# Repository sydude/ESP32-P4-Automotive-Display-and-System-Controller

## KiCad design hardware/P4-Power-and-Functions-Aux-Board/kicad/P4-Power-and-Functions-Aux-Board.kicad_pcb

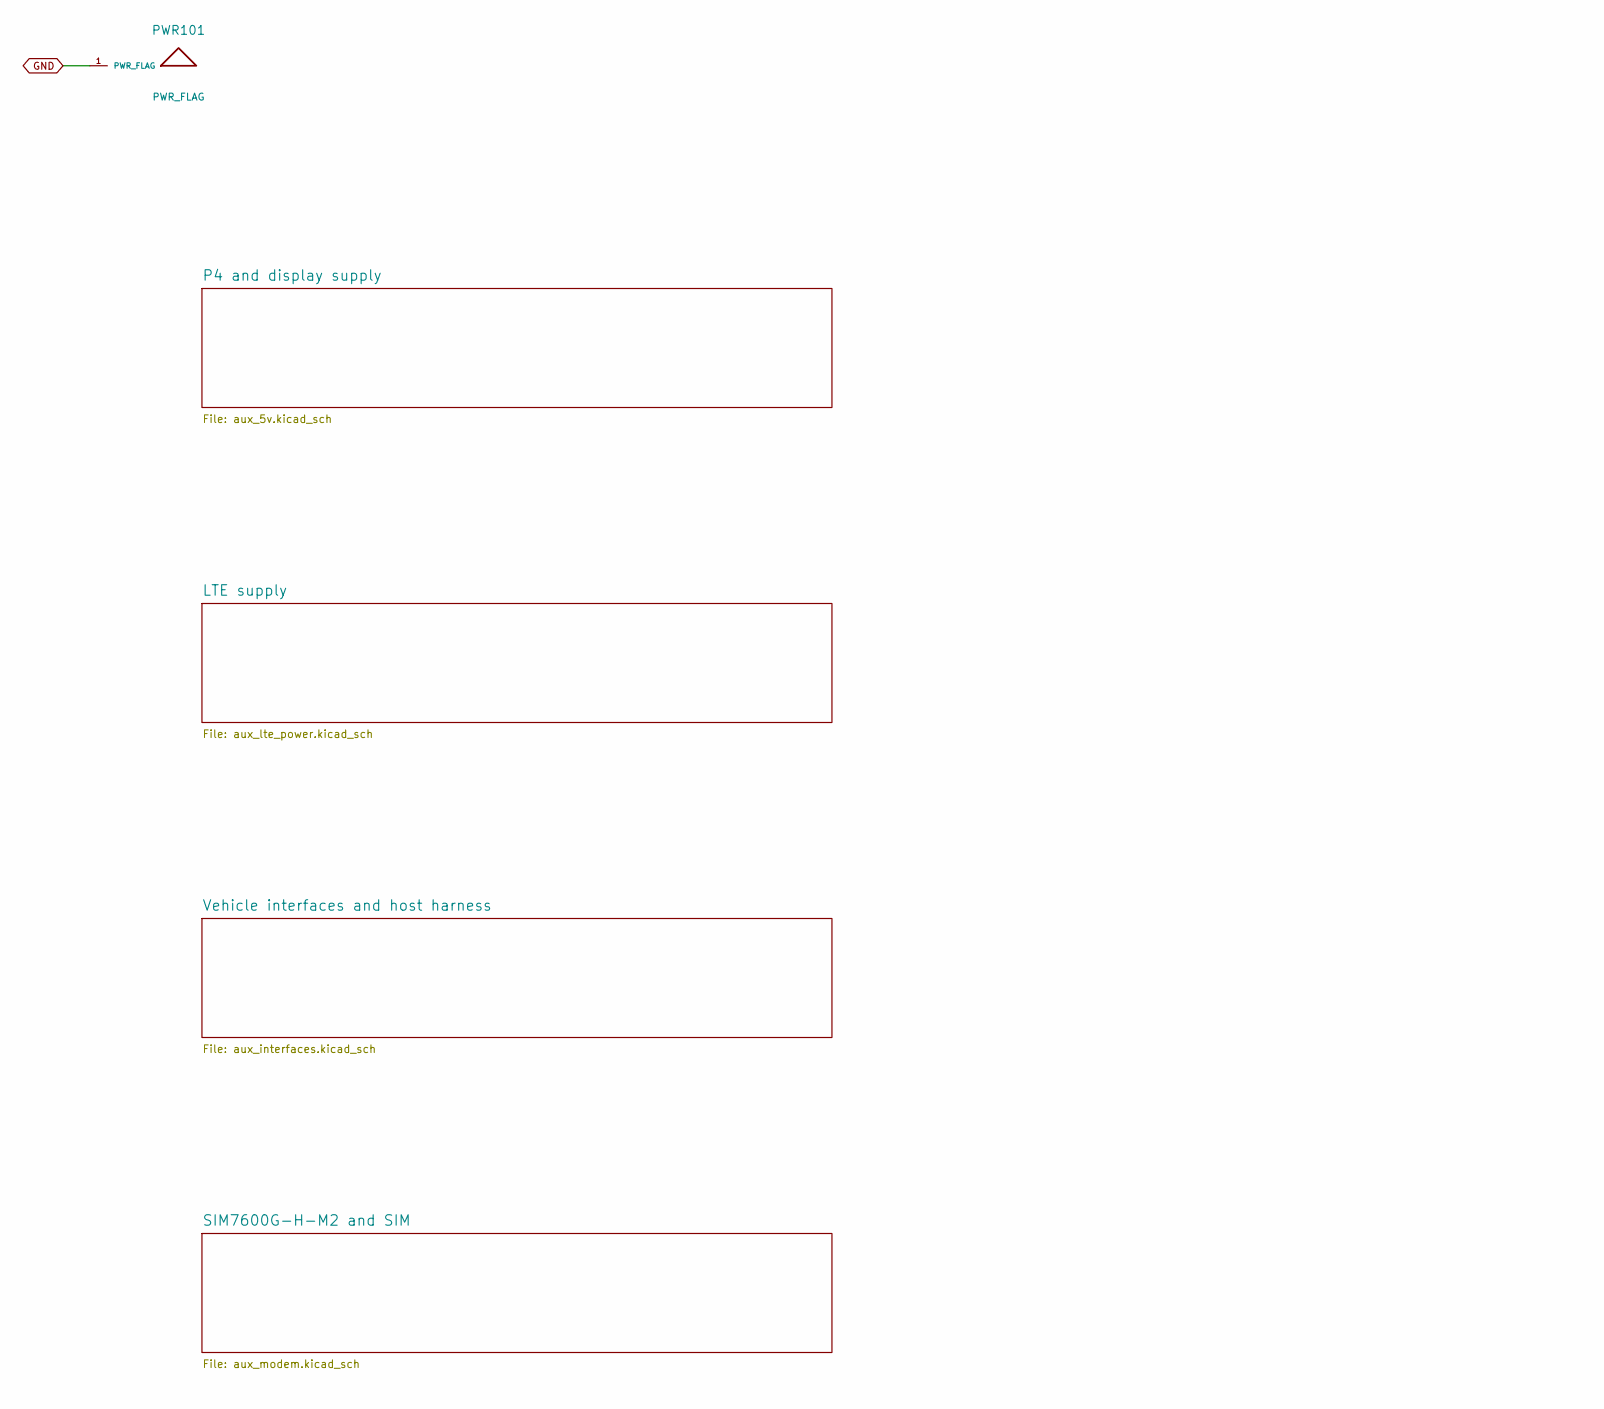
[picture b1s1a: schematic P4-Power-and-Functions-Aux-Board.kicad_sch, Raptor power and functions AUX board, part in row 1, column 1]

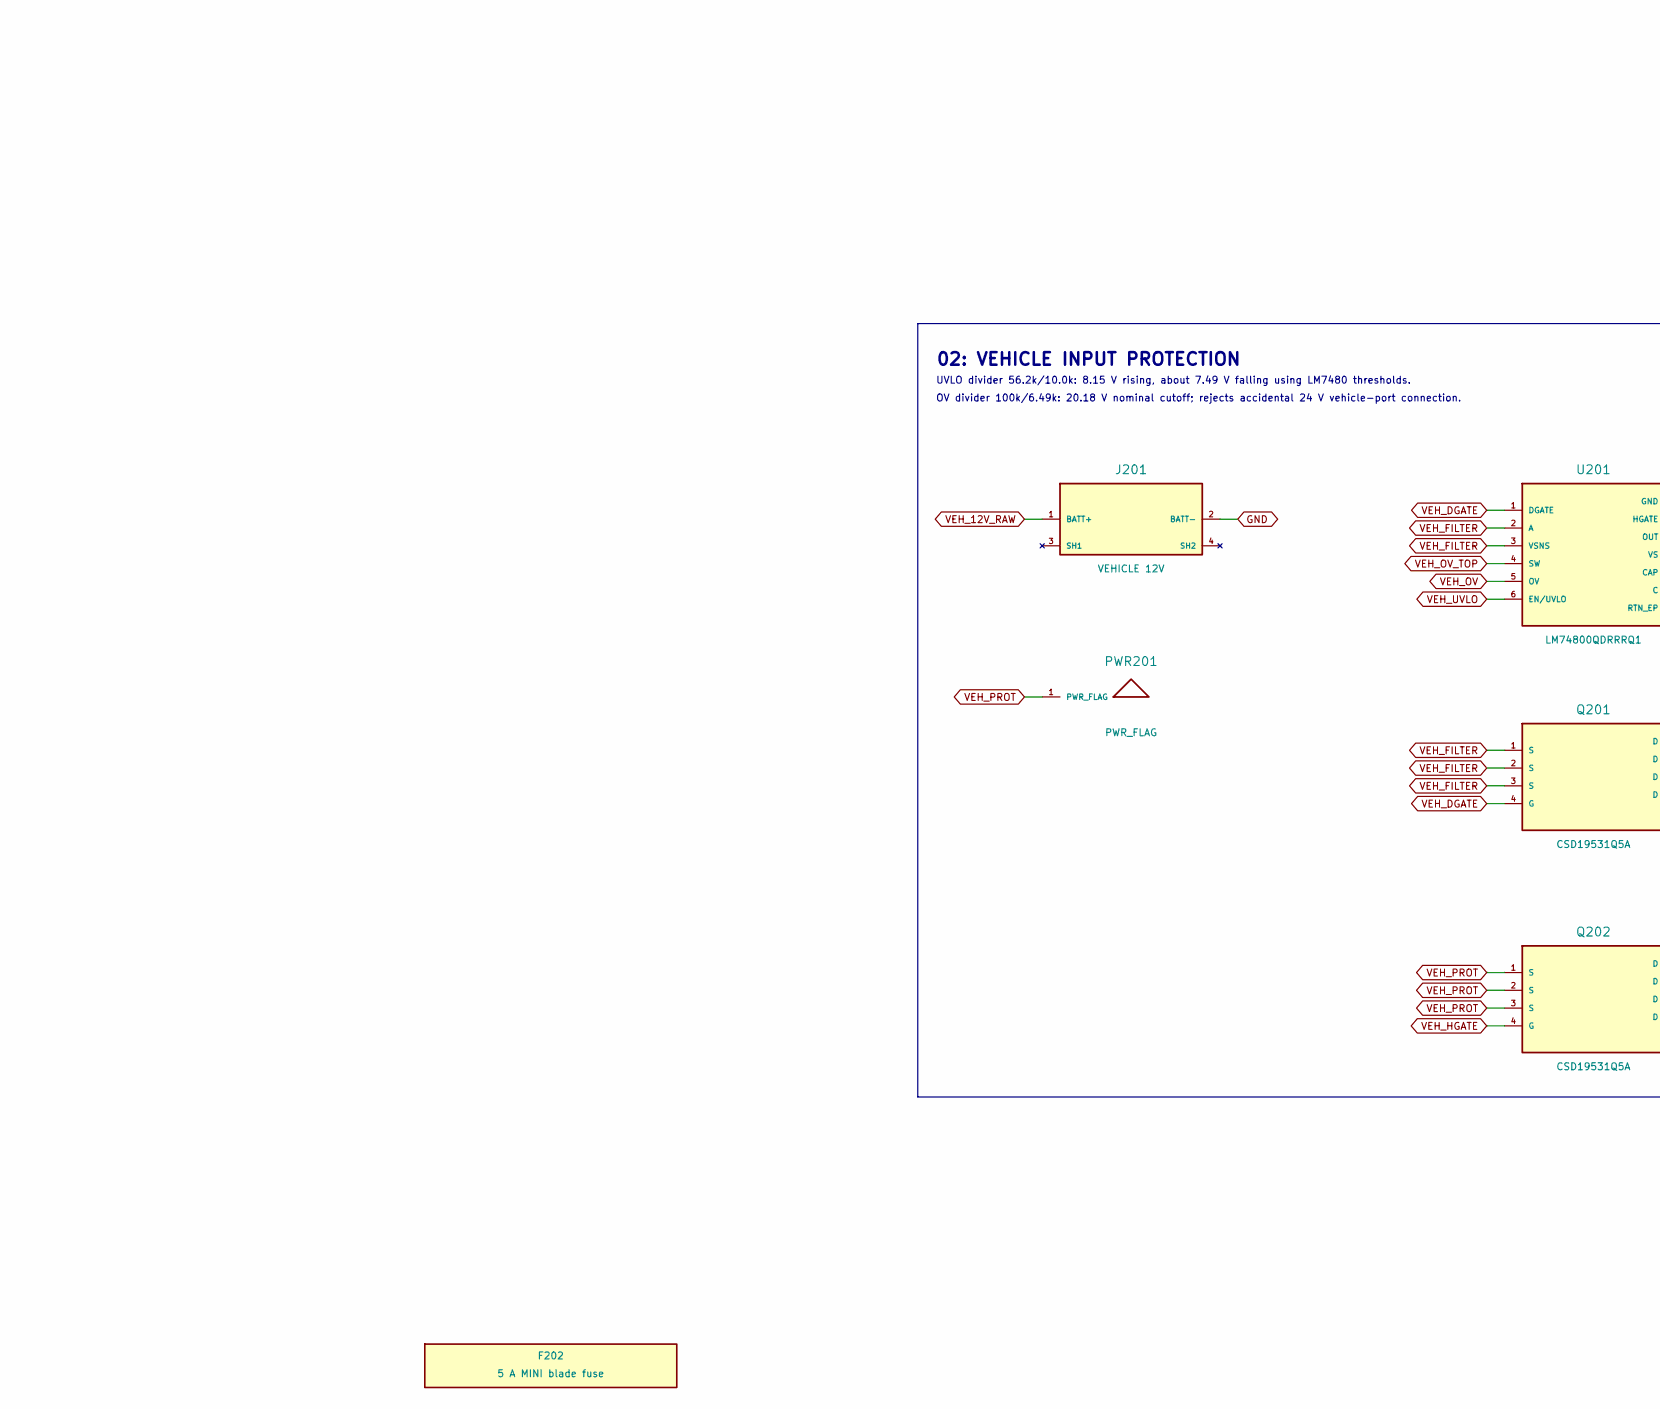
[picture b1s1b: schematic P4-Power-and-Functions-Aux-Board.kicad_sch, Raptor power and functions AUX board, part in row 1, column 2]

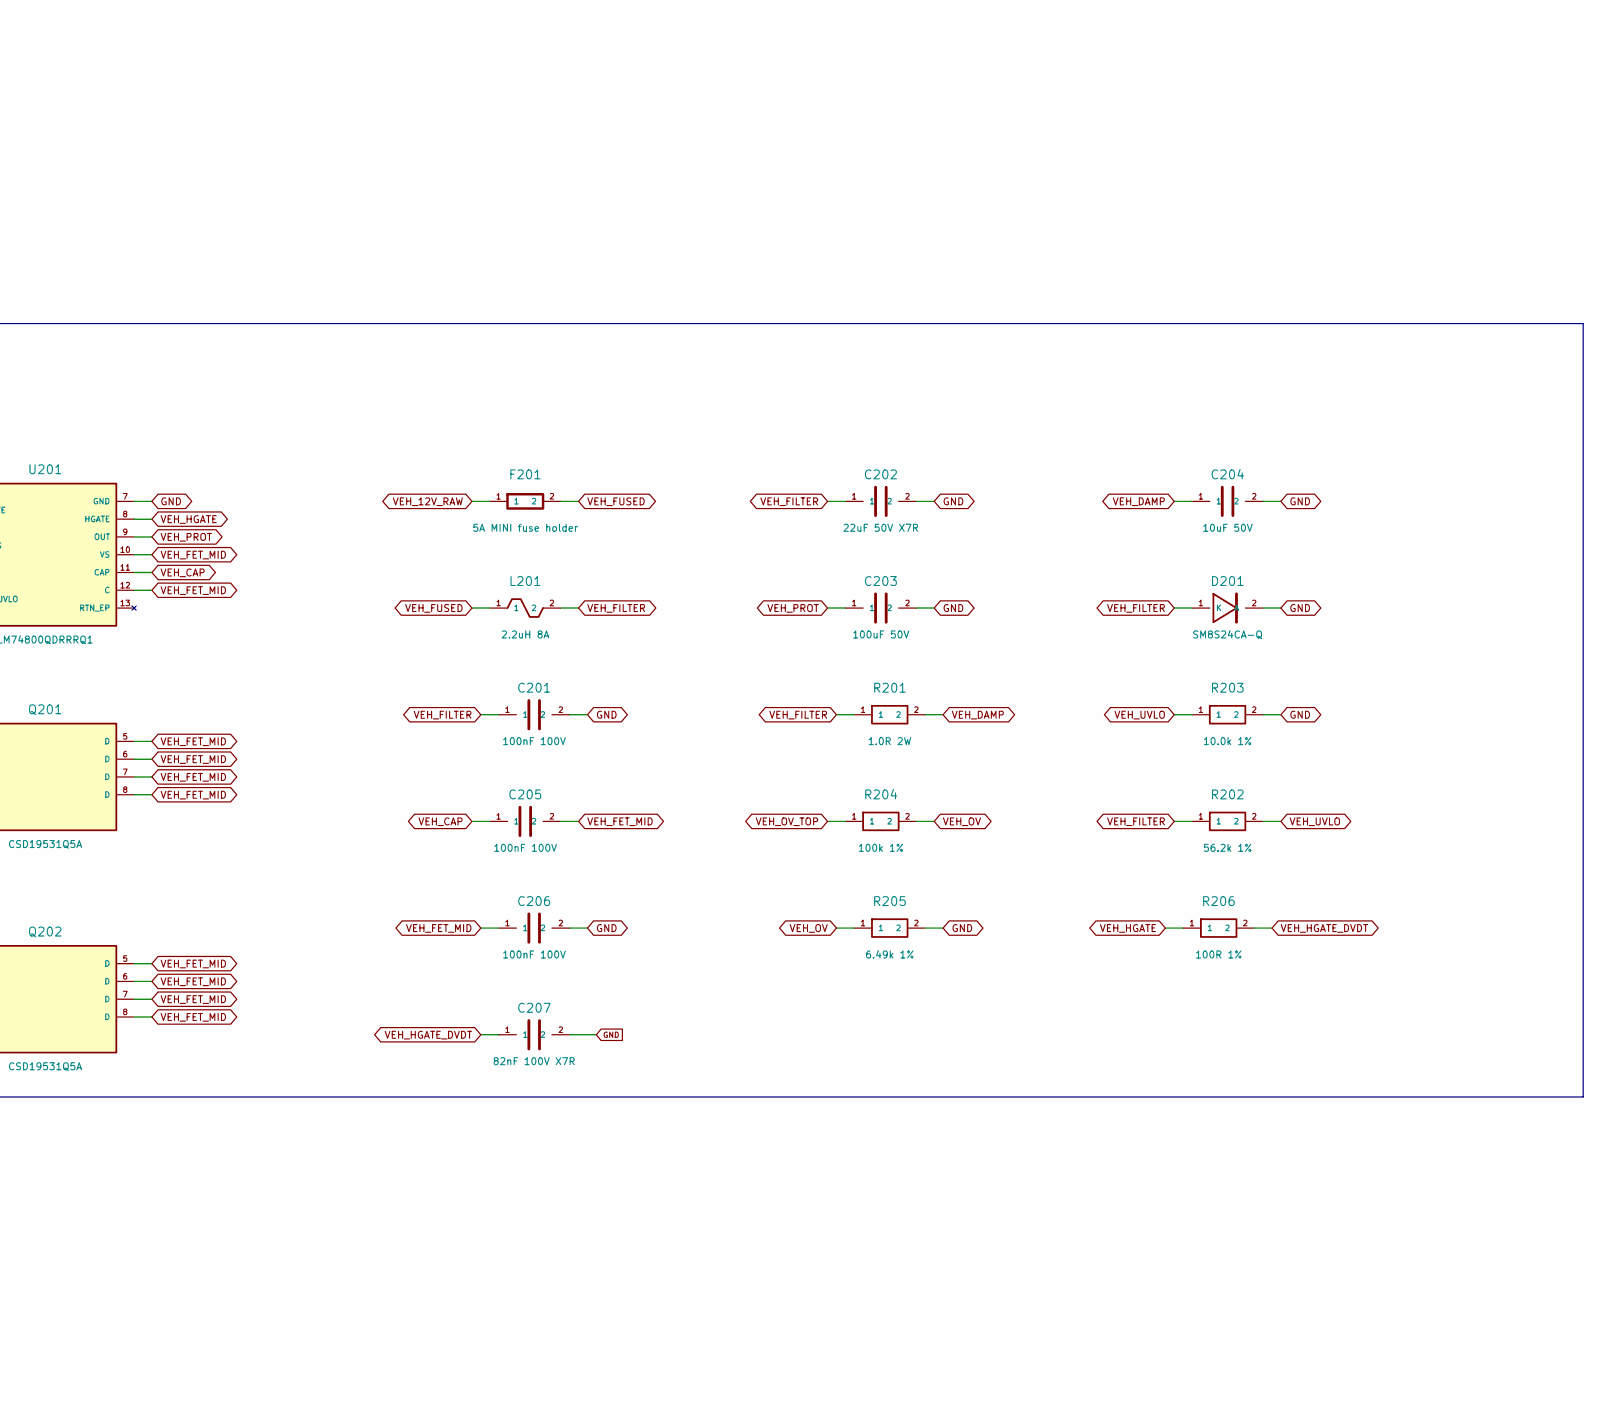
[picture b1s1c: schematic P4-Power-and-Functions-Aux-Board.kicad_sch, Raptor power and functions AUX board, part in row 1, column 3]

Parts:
C201, C205, C206: 100nF 100V; C_0603_1608Metric; MPN GCM188R72A104KA64D; LCSC C415406
C202: 22uF 50V X7R; C_1812_4532Metric; MPN FS43X226K500ERG; LCSC C22388553
C203: 100uF 50V; CP_Elec_10x10; MPN MAL215097101E3; LCSC C2163037
C204: 10uF 50V; C_1210_3225Metric; MPN GRM32ER71H106KA12L; LCSC C77102
C207: 82nF 100V X7R; C_0603_1608Metric; MPN C0603C823K1RACAUTO; LCSC C19862796
D201: SM8S24CA-Q; Bourns_DO-218AB; MPN SM8S24CA-Q; LCSC C1976790
F201: 5A MINI fuse holder; Fuseholder_Blade_Mini_Keystone_3568; MPN 3568; LCSC C5249699
F202: 5 A MINI blade fuse; MPN 0297005.WXNV; LCSC C151093
J201: VEHICLE 12V; CONN_SD-43045-007_02_MOL; MPN 43045-0218; LCSC C476811
L201: 2.2uH 8A; L_Bourns_SRP1038A_10.0x10.0mm; MPN SRP1038A-2R2M; LCSC C2042353
PWR101, PWR201: PWR_FLAG
Q201, Q202: CSD19531Q5A; Texas_DQJ0008A_VSONP-8; MPN CSD19531Q5A; LCSC C2760462
R201: 1.0R 2W; R_2512_6332Metric; MPN CRH2512F1R00E04S; LCSC C2832126
R202: 56.2k 1%; R_0603_1608Metric; MPN AF0603FR-0756K2L; LCSC C1882617
R203: 10.0k 1%; R_0603_1608Metric; MPN AC0603FR-0710KL; LCSC C116677
R204: 100k 1%; R_0603_1608Metric; MPN AC0603FR-07100KL; LCSC C116674
R205: 6.49k 1%; R_0603_1608Metric; MPN RC0603FR-076K49L; LCSC C163421
R206: 100R 1%; R_0603_1608Metric; MPN ERJ-3EKF1000V; LCSC C193336
U201: LM74800QDRRRQ1; Texas_DRR0012E_WSON-12_3x3mm_P0.5mm_EP1.3x2.5mm; MPN LM74800QDRRRQ1; LCSC C3215600

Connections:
GND: C201.2, C202.2, C203.2, C204.2, C206.2, C207.2, D201.2 (A), J201.2 (BATT-), PWR101.1, R203.2, R205.2, U201.7 (GND); also elsewhere on the board
VEH_12V_RAW: F201.1, J201.1 (BATT+)
VEH_CAP: C205.1, U201.11 (CAP)
VEH_DAMP: C204.1, R201.2
VEH_DGATE: Q201.4 (G), U201.1 (DGATE)
VEH_FET_MID: C205.2, C206.1, Q201.5 (D), Q201.6 (D), Q201.7 (D), Q201.8 (D), Q202.5 (D), Q202.6 (D), Q202.7 (D), Q202.8 (D), U201.10 (VS), U201.12 (C)
VEH_FILTER: C201.1, C202.1, D201.1 (K), L201.2, Q201.1 (S), Q201.2 (S), Q201.3 (S), R201.1, R202.1, U201.2 (A), U201.3 (VSNS)
VEH_FUSED: F201.2, L201.1
VEH_HGATE: Q202.4 (G), R206.1, U201.8 (HGATE)
VEH_HGATE_DVDT: C207.1, R206.2
VEH_OV: R204.2, R205.1, U201.5 (OV)
VEH_OV_TOP: R204.1, U201.4 (SW)
VEH_PROT: C203.1, PWR201.1, Q202.1 (S), Q202.2 (S), Q202.3 (S), U201.9 (OUT); also elsewhere on the board
VEH_UVLO: R202.2, R203.1, U201.6 (EN/UVLO)

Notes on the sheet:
02: VEHICLE INPUT PROTECTION
OV divider 100k/6.49k: 20.18 V nominal cutoff; rejects accidental 24 V vehicle-port connection.
UVLO divider 56.2k/10.0k: 8.15 V rising, about 7.49 V falling using LM7480 thresholds.

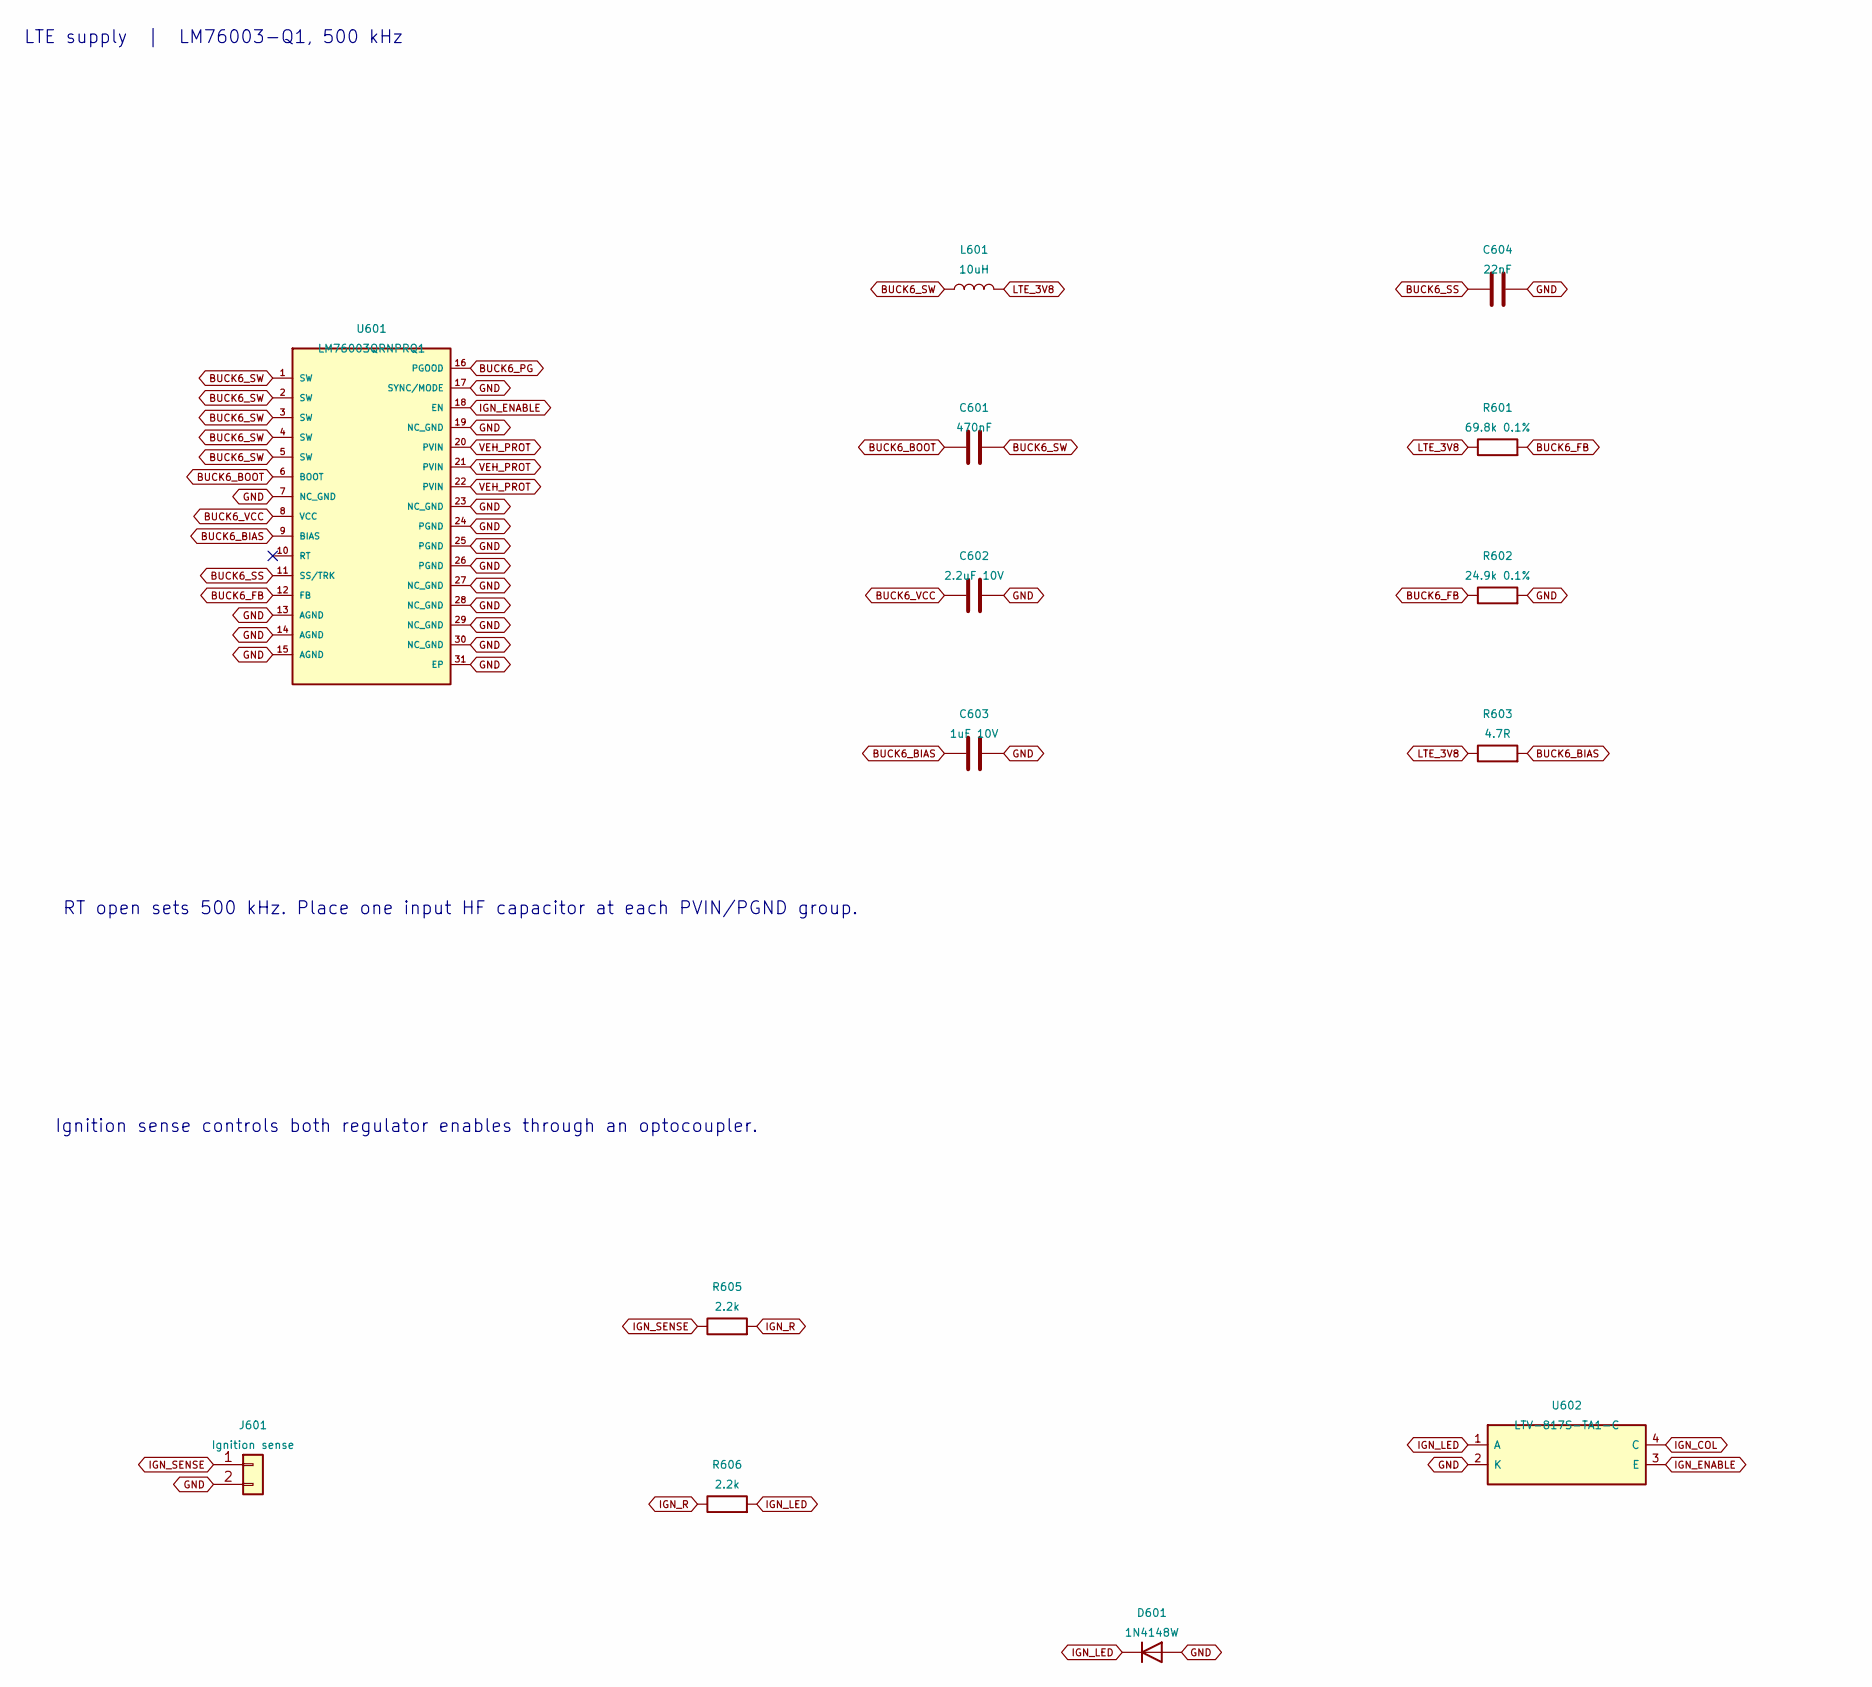
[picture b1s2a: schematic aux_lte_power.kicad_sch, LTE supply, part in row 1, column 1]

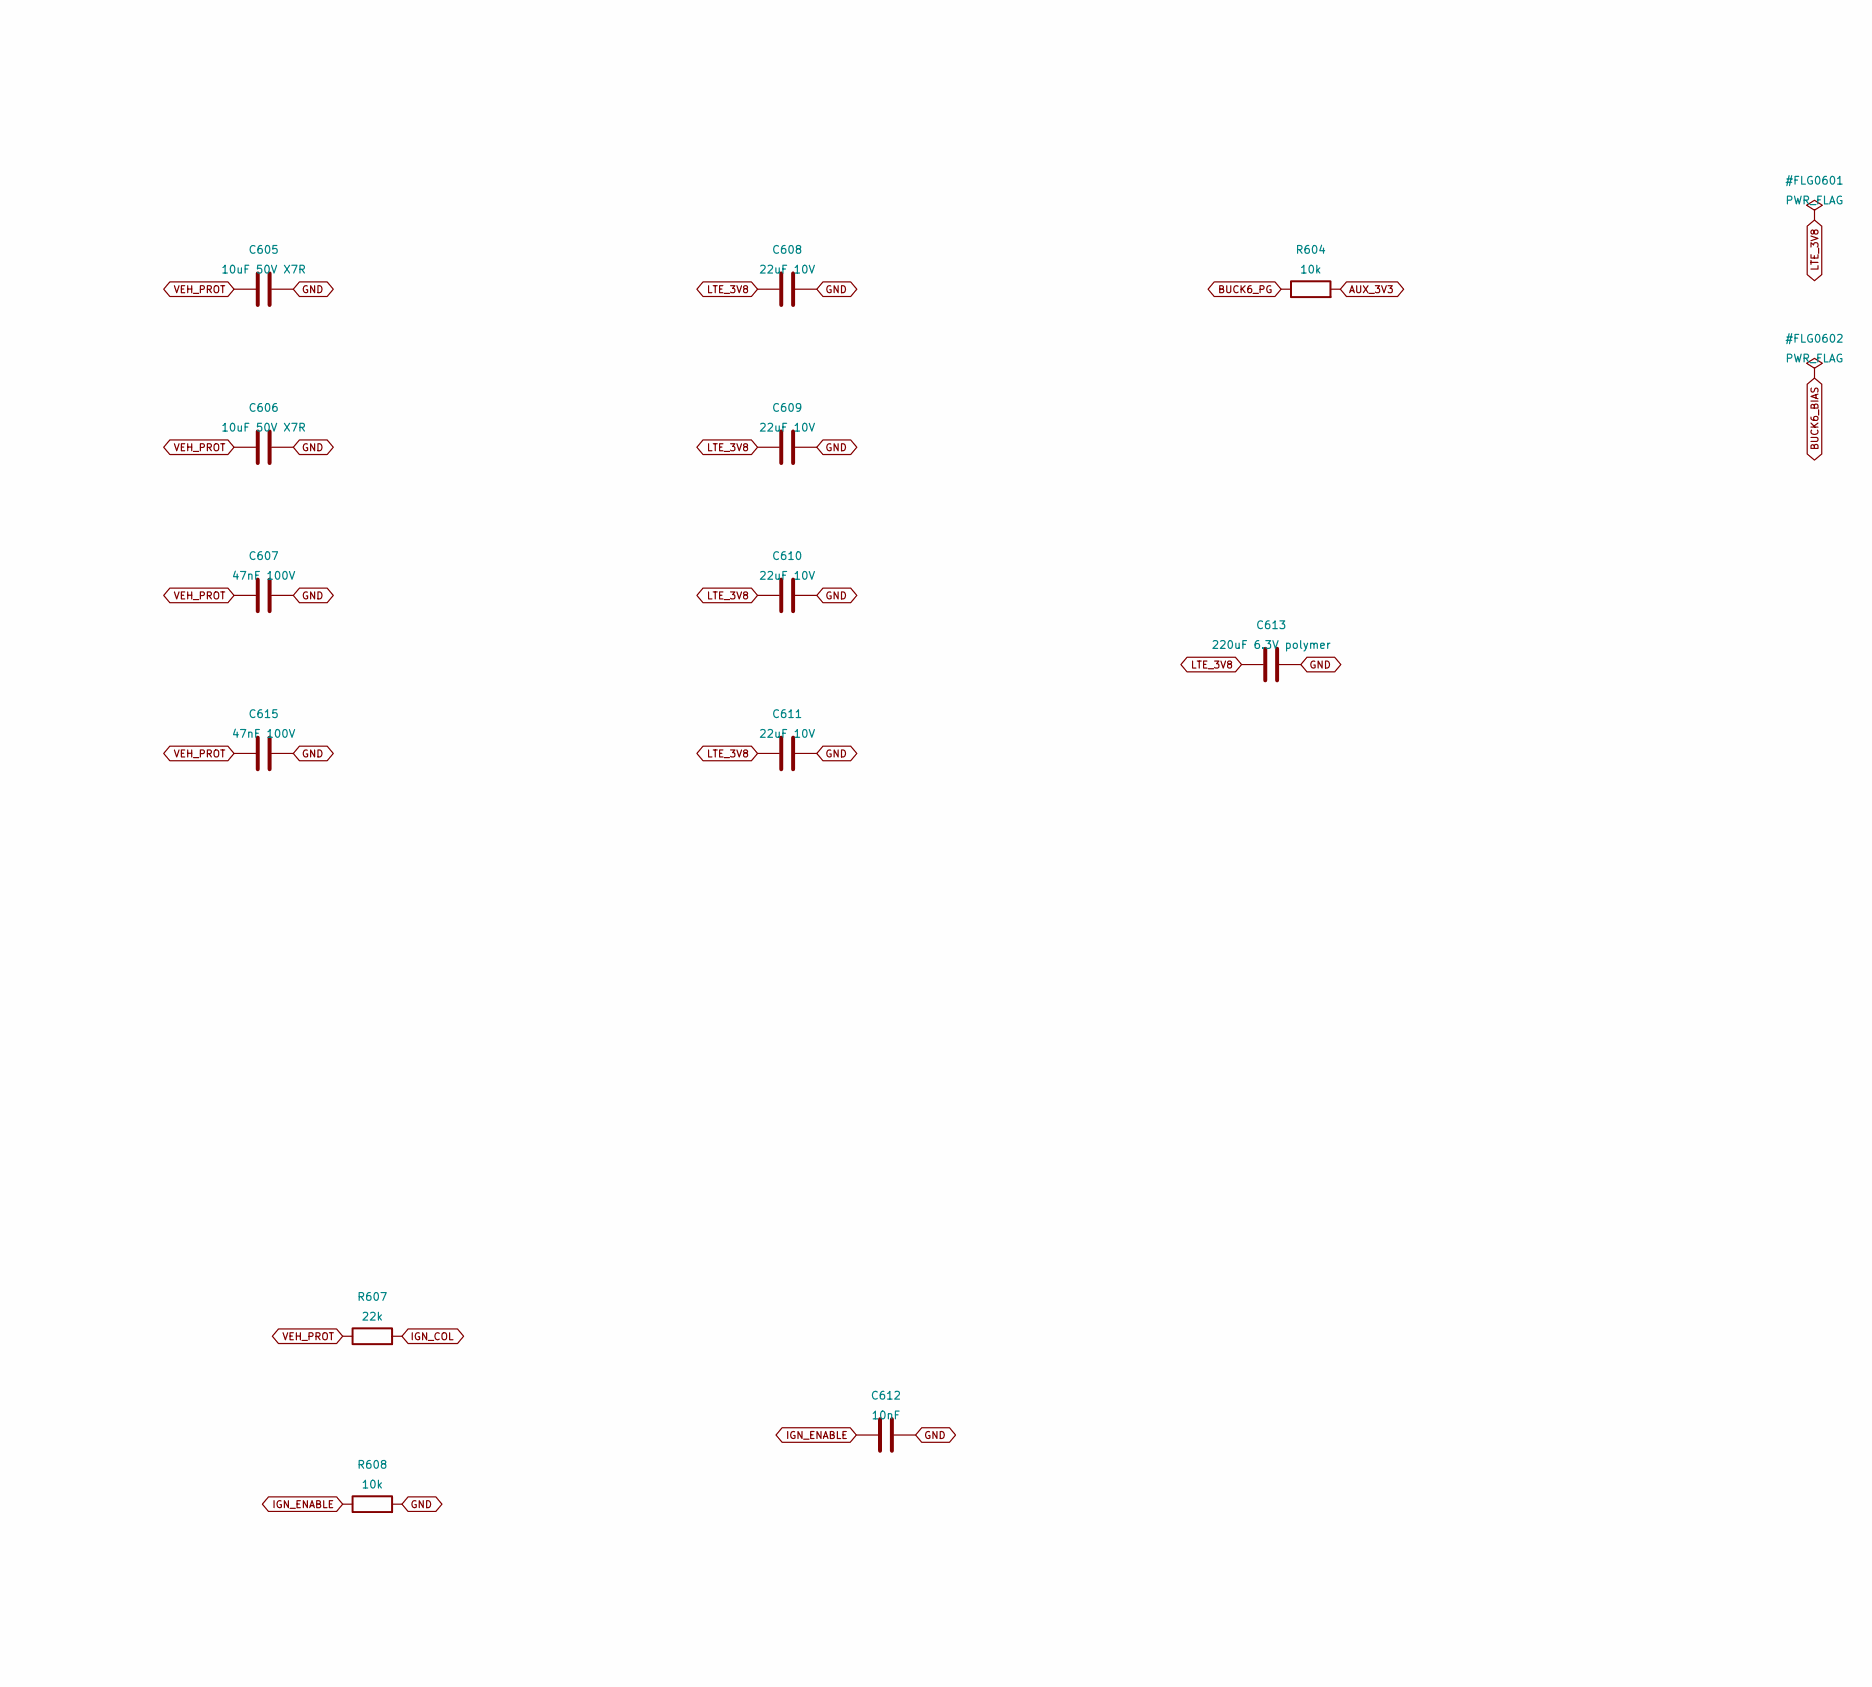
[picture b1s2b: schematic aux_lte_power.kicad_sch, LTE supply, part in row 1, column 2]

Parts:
C601: 470nF; C_0603_1608Metric; MPN GRM188R71E474KA12D; LCSC C77052
C602: 2.2uF 10V; C_0603_1608Metric; MPN GRM188R71A225KE15D; LCSC C86018
C603: 1uF 10V; C_0603_1608Metric; MPN GCM188R71C105KA64D; LCSC C161212
C604: 22nF; C_0603_1608Metric; MPN GRM188R71H223KA01D; LCSC C77056
C605, C606: 10uF 50V X7R; C_1210_3225Metric; MPN GRM32ER71H106KA12L; LCSC C77102
C607, C615: 47nF 100V; C_0603_1608Metric; MPN C0603C473K1RAC7867; LCSC C3881354
C608, C609, C610, C611: 22uF 10V; C_1210_3225Metric; MPN GCM32ER71A226KE12L; LCSC C913632
C612: 10nF; C_0603_1608Metric; MPN GCM188R71H103KA37D; LCSC C85863
C613: 220uF 6.3V polymer; CP_Elec_6.3x5.9; MPN 6SVPC220M; LCSC C2162098
D601: 1N4148W; D_SOD-123; MPN 1N4148W-7-F; LCSC C83528
J601: Ignition sense; Molex_SL_171971-0002_1x02_P2.54mm_Vertical; MPN 171971-0002
L601: 10uH; L_Coilcraft_XAL7070-XXX; MPN XAL7070-103MEC; LCSC C55598417
R601: 69.8k 0.1%; R_0603_1608Metric; MPN ERA-3AEB6982V; LCSC C3924043
R602: 24.9k 0.1%; R_0603_1608Metric; MPN TR0603B24K9P0525Z; LCSC C149931
R603: 4.7R; R_0603_1608Metric; MPN AC0603FR-074R7L; LCSC C144651
R604, R608: 10k; R_0603_1608Metric; MPN AC0603FR-0710KL; LCSC C116677
R605, R606: 2.2k; R_1206_3216Metric; MPN AC1206FR-072K2L; LCSC C229510
R607: 22k; R_0603_1608Metric; MPN AC0603FR-0722KL; LCSC C144680
U601: LM76003QRNPRQ1; Texas_RNP0030B_WQFN-30-1EP_4x6mm_P0.5mm_EP1.8x4.5mm_Thermal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; MPN LM76003QRNPRQ1; LCSC C2073028
U602: LTV-817S-TA1-C; SMDIP-4_W9.53mm; MPN LTV-817S-TA1-C; LCSC C109227

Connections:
AUX_3V3: R604.2; also elsewhere on the board
BUCK6_BIAS: C603.1, R603.2, U601.9 (BIAS)
BUCK6_BOOT: C601.1, U601.6 (BOOT)
BUCK6_FB: R601.2, R602.1, U601.12 (FB)
BUCK6_PG: R604.1, U601.16 (PGOOD); also elsewhere on the board
BUCK6_SS: C604.1, U601.11 (SS/TRK)
BUCK6_SW: C601.2, L601.1, U601.1 (SW), U601.2 (SW), U601.3 (SW), U601.4 (SW), U601.5 (SW)
BUCK6_VCC: C602.1, U601.8 (VCC)
GND: C602.2, C603.2, C604.2, C605.2, C606.2, C607.2, C608.2, C609.2, C610.2, C611.2, C612.2, C613.2, C615.2, D601.2 (A), J601.2, R602.2, R608.2, U601.7 (NC_GND), U601.13 (AGND), U601.14 (AGND), U601.15 (AGND), U601.17 (SYNC/MODE), U601.19 (NC_GND), U601.23 (NC_GND), U601.24 (PGND), U601.25 (PGND), U601.26 (PGND), U601.27 (NC_GND), U601.28 (NC_GND), U601.29 (NC_GND), U601.30 (NC_GND), U601.31 (EP), U602.2 (K); also elsewhere on the board
IGN_COL: R607.2, U602.4 (C)
IGN_ENABLE: C612.1, R608.1, U601.18 (EN), U602.3 (E); also elsewhere on the board
IGN_LED: D601.1 (K), R606.2, U602.1 (A)
IGN_R: R605.2, R606.1
IGN_SENSE: J601.1, R605.1
LTE_3V8: C608.1, C609.1, C610.1, C611.1, C613.1, L601.2, R601.1, R603.1; also elsewhere on the board
VEH_PROT: C605.1, C606.1, C607.1, C615.1, R607.1, U601.20 (PVIN), U601.21 (PVIN), U601.22 (PVIN); also elsewhere on the board

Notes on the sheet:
RT open sets 500 kHz. Place one input HF capacitor at each PVIN/PGND group.
Ignition sense controls both regulator enables through an optocoupler.
LTE supply | LM76003-Q1, 500 kHz
